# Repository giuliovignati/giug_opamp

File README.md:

# GiugPamp: a BJT based discrete component made operational amplifier
---

## GiugPamp 101

#### GiugPamp 101 Schematic

#### GiugPamp 101 PCB

## GiugPamp 301

#### GiugPamp 301 Schematic

#### GiugPamp 301 PCB

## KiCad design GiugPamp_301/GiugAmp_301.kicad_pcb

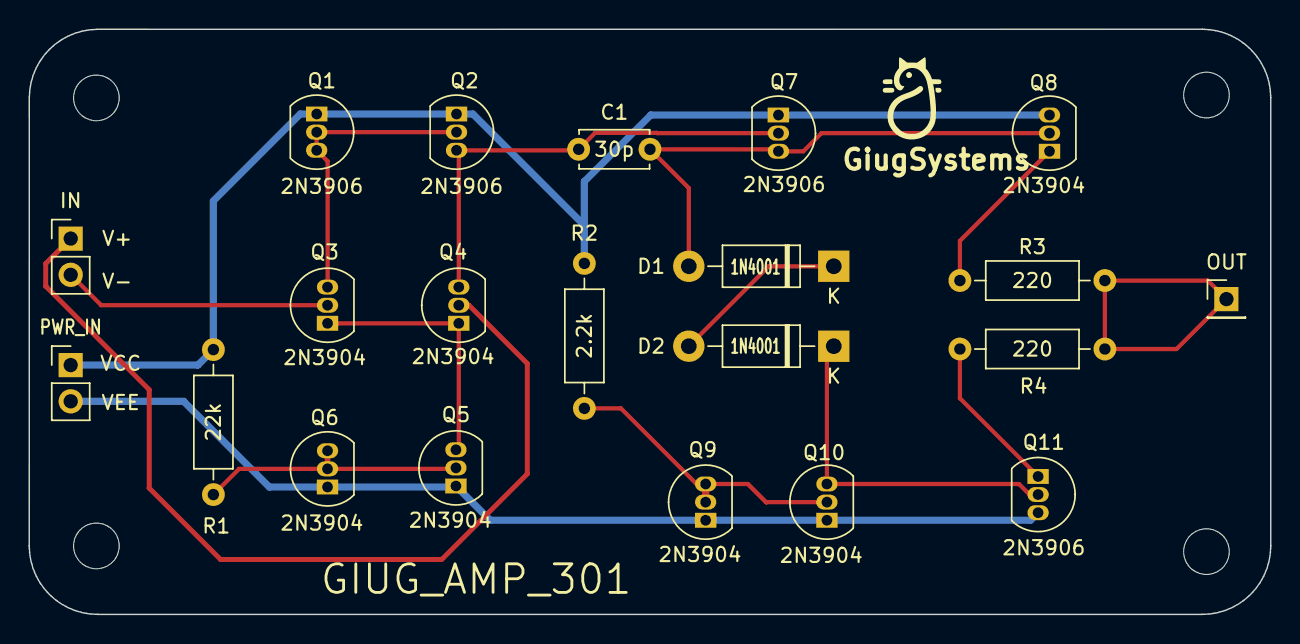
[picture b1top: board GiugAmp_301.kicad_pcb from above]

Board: 2 copper layers, 87.0 x 41.0 mm, 25 parts (0 on the bottom side), 15 nets.

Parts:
C1: 30p; C_Disc_D4.7mm_W2.5mm_P5.00mm
D1, D2: 1N4001; D_DO-41_SOD81_P10.16mm_Horizontal
H1, H2, H3, H4: MountingHole; MountingHole_3.2mm_M3
IN: Conn_01x02_Pin; PinHeader_1x02_P2.54mm_Vertical
OUT: Conn_01x01_Pin; PinHeader_1x01_P2.54mm_Vertical
PWR_IN: Conn_01x02_Pin; PinHeader_1x02_P2.54mm_Vertical
Q1, Q2, Q7, Q11: 2N3906; TO-92_Inline
Q3, Q4, Q5, Q6, Q8, Q9, Q10: 2N3904; TO-92_Inline
R1: 22k; R_Axial_DIN0207_L6.3mm_D2.5mm_P10.16mm_Horizontal
R2: 2.2k; R_Axial_DIN0207_L6.3mm_D2.5mm_P10.16mm_Horizontal
R3, R4: 220; R_Axial_DIN0207_L6.3mm_D2.5mm_P10.16mm_Horizontal

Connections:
unnamed: C1.1, D1.2 (A), Q7.3 (C), Q8.2 (B)
unnamed: D1.1 (K), D2.2 (A)
unnamed: D2.1 (K), Q10.3 (C), Q11.2 (B)
unnamed: Q1.2 (B), Q1.3 (C), Q2.2 (B), Q3.3 (C)
unnamed: C1.2, Q2.3 (C), Q4.3 (C), Q7.2 (B)
unnamed: Q3.1 (E), Q4.1 (E), Q5.3 (C)
unnamed: Q5.2 (B), Q6.2 (B), Q6.3 (C), R1.2
unnamed: Q8.1 (E), R3.1
unnamed: Q9.2 (B), Q9.3 (C), Q10.2 (B), R2.2
unnamed: Q11.1 (E), R4.2
OUT: OUT.1, R3.2, R4.1
V+: IN.1, Q4.2 (B)
V-: IN.2, Q3.2 (B)
VCC: PWR_IN.1, Q1.1 (E), Q2.1 (E), Q7.1 (E), Q8.3 (C), R1.1, R2.1
VEE: PWR_IN.2, Q5.1 (E), Q6.1 (E), Q9.1 (E), Q10.1 (E), Q11.3 (C)

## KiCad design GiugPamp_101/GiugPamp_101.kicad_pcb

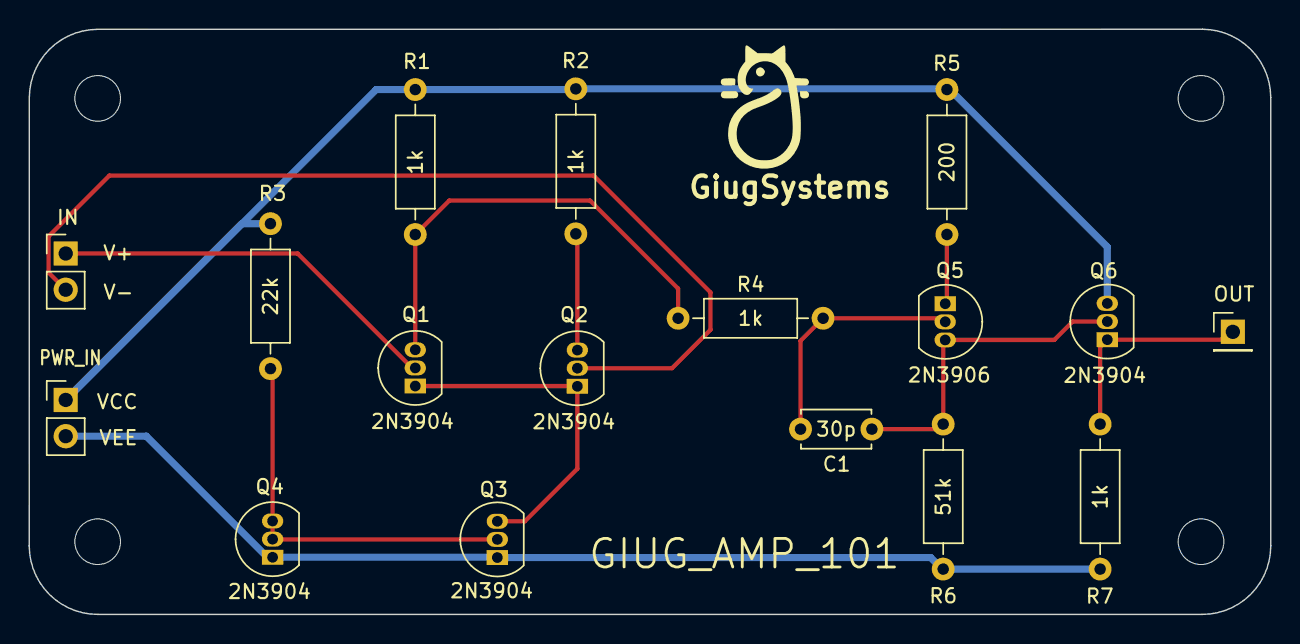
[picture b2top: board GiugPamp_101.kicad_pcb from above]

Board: 2 copper layers, 87.0 x 41.0 mm, 21 parts (0 on the bottom side), 12 nets.

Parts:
C1: 30p; C_Disc_D4.7mm_W2.5mm_P5.00mm
H1, H2, H3, H4: MountingHole; MountingHole_3.2mm_M3
IN: Conn_01x02_Pin; PinHeader_1x02_P2.54mm_Vertical
OUT: Conn_01x01_Pin; PinHeader_1x01_P2.54mm_Vertical
PWR_IN: Conn_01x02_Pin; PinHeader_1x02_P2.54mm_Vertical
Q1, Q2, Q3, Q4, Q6: 2N3904; TO-92_Inline
Q5: 2N3906; TO-92_Inline
R1, R2, R4, R7: 1k; R_Axial_DIN0207_L6.3mm_D2.5mm_P10.16mm_Horizontal
R3: 22k; R_Axial_DIN0207_L6.3mm_D2.5mm_P10.16mm_Horizontal
R5: 200; R_Axial_DIN0207_L6.3mm_D2.5mm_P10.16mm_Horizontal
R6: 51k; R_Axial_DIN0207_L6.3mm_D2.5mm_P10.16mm_Horizontal

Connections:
unnamed: Q1.3 (C), R1.2, R4.1
unnamed: Q1.1 (E), Q2.1 (E), Q3.3 (C)
unnamed: Q2.3 (C), R2.2
unnamed: Q3.2 (B), Q4.2 (B), Q4.3 (C), R3.2
unnamed: C1.2, Q5.2 (B), R4.2
unnamed: C1.1, Q5.3 (C), Q6.2 (B), R6.2
unnamed: Q5.1 (E), R5.1
OUT: OUT.1, Q6.1 (E), R7.2
V+: IN.1, Q1.2 (B)
V-: IN.2, Q2.2 (B)
VCC: PWR_IN.1, Q6.3 (C), R1.1, R2.1, R3.1, R5.2
VEE: PWR_IN.2, Q3.1 (E), Q4.1 (E), R6.1, R7.1

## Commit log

2024-12-22 final versions for basic 2 layer operational amplifiers
2025-04-29 added simulation files for lt spice
